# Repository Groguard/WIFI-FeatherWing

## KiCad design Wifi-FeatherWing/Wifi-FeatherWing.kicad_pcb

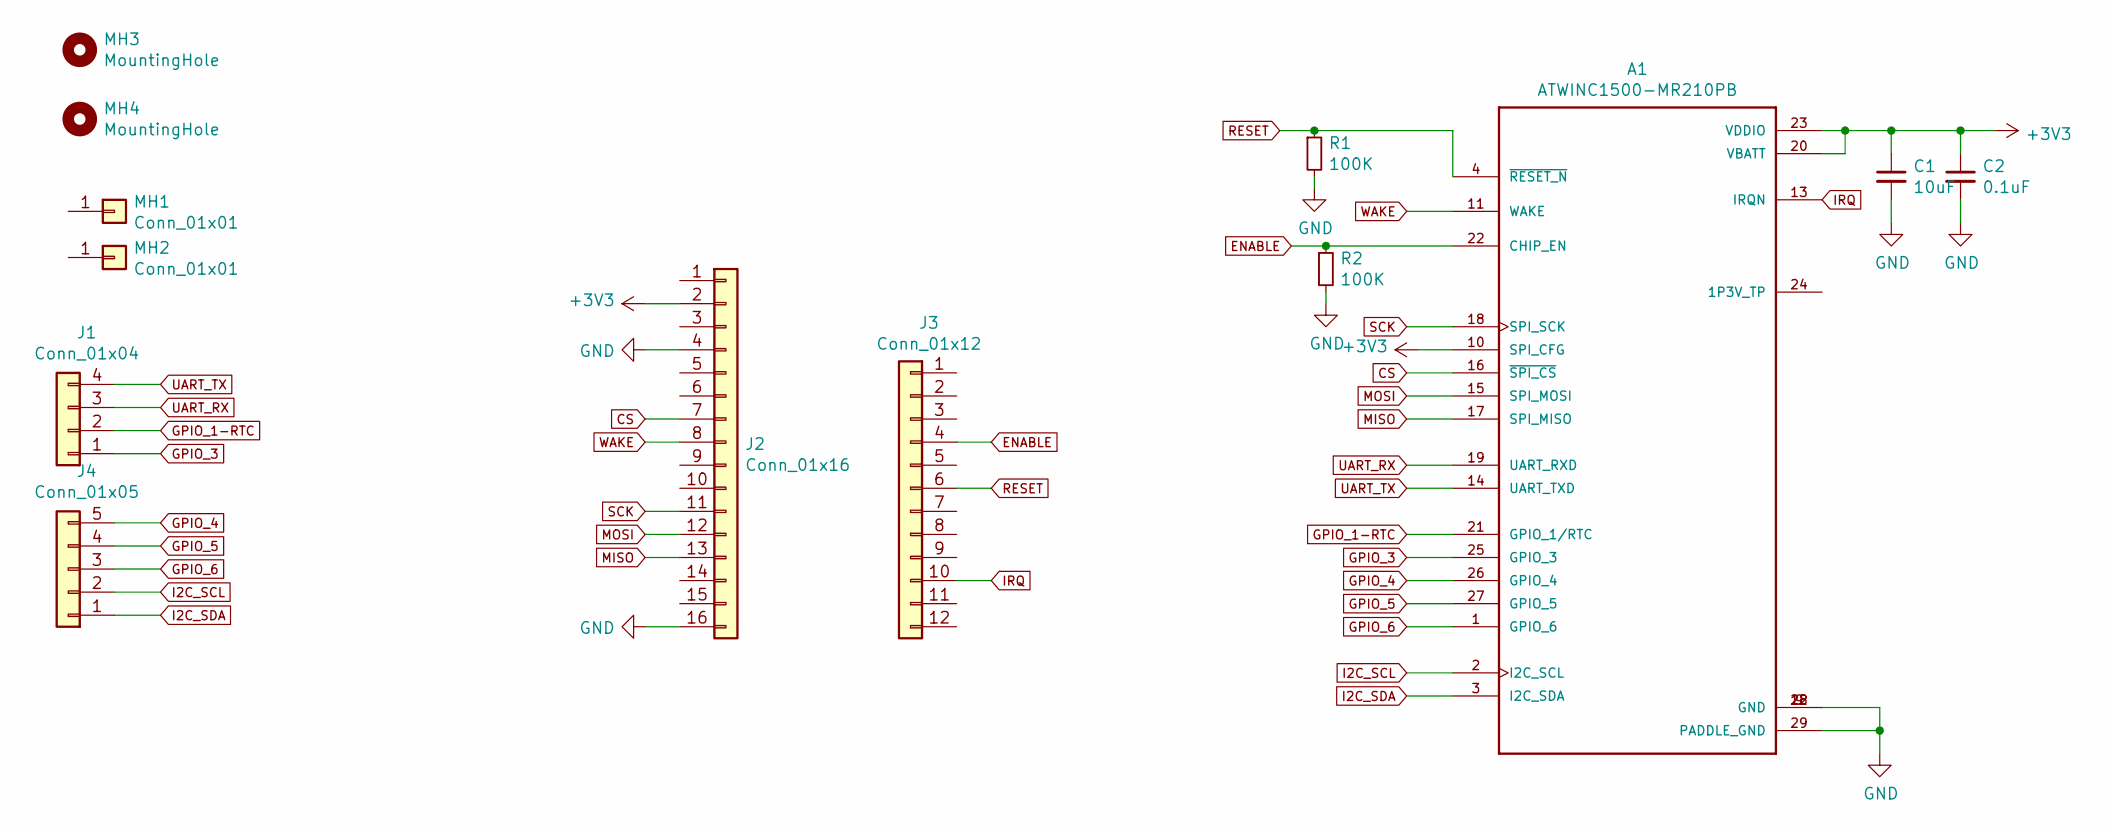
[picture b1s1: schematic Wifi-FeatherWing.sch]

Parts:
A1: ATWINC1500-MR210PB; XCVR_ATWINC1500-MR210PB
C1: 10uF; C_0805_2012Metric
C2: 0.1uF; C_0402_1005Metric
J1: Conn_01x04; PinHeader_1x04_P2.54mm_Vertical
J2: Conn_01x16; PinHeader_1x16_P2.54mm_Vertical
J3: Conn_01x12; PinHeader_1x12_P2.54mm_Vertical
J4: Conn_01x05; PinHeader_1x05_P2.54mm_Vertical
MH1, MH2: Conn_01x01; MountingHole_2.7mm_M2.5_DIN965_Pad
MH3, MH4: MountingHole; MountingHole_2.7mm_M2.5
R1, R2: 100K; R_0805_2012Metric

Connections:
+3V3: A1.10 (SPI_CFG), A1.20 (VBATT), A1.23 (VDDIO), C1.1, C2.1, J2.2
CS: A1.16 (~SPI_CS~), J2.7
ENABLE: A1.22 (CHIP_EN), J3.4, R2.1
GND: A1.9 (GND), A1.12 (GND), A1.28 (GND), A1.29 (PADDLE_GND), C1.2, C2.2, J2.4, J2.16, R1.2, R2.2
GPIO_1-RTC: A1.21 (GPIO_1/RTC), J1.2
GPIO_3: A1.25 (GPIO_3), J1.1
GPIO_4: A1.26 (GPIO_4), J4.5
GPIO_5: A1.27 (GPIO_5), J4.4
GPIO_6: A1.1 (GPIO_6), J4.3
I2C_SCL: A1.2 (I2C_SCL), J4.2
I2C_SDA: A1.3 (I2C_SDA), J4.1
IRQ: A1.13 (IRQN), J3.10
MISO: A1.17 (SPI_MISO), J2.13
MOSI: A1.15 (SPI_MOSI), J2.12
RESET: A1.4 (~RESET_N~), J3.6, R1.1
SCK: A1.18 (SPI_SCK), J2.11
UART_RX: A1.19 (UART_RXD), J1.3
UART_TX: A1.14 (UART_TXD), J1.4
WAKE: A1.11 (WAKE), J2.8

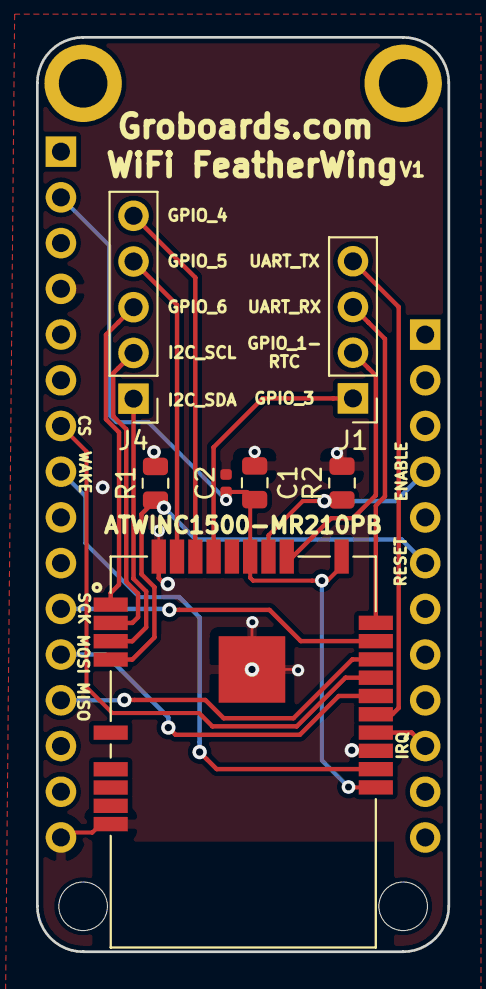
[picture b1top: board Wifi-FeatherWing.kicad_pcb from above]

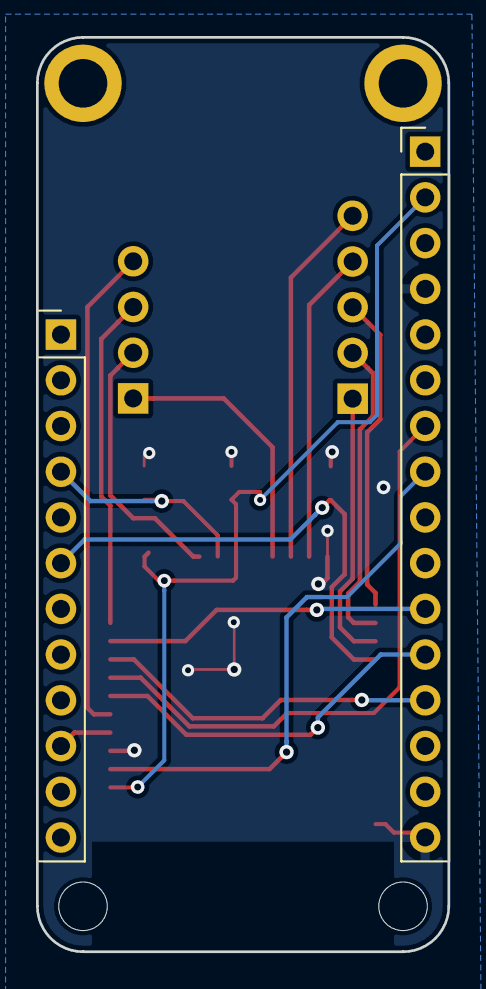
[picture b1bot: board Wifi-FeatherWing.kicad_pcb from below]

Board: 2 copper layers, 22.9 x 50.8 mm, 13 parts (2 on the bottom side), 19 nets.

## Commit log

2020-01-31 Add WiFi FeatherWing Schematic
